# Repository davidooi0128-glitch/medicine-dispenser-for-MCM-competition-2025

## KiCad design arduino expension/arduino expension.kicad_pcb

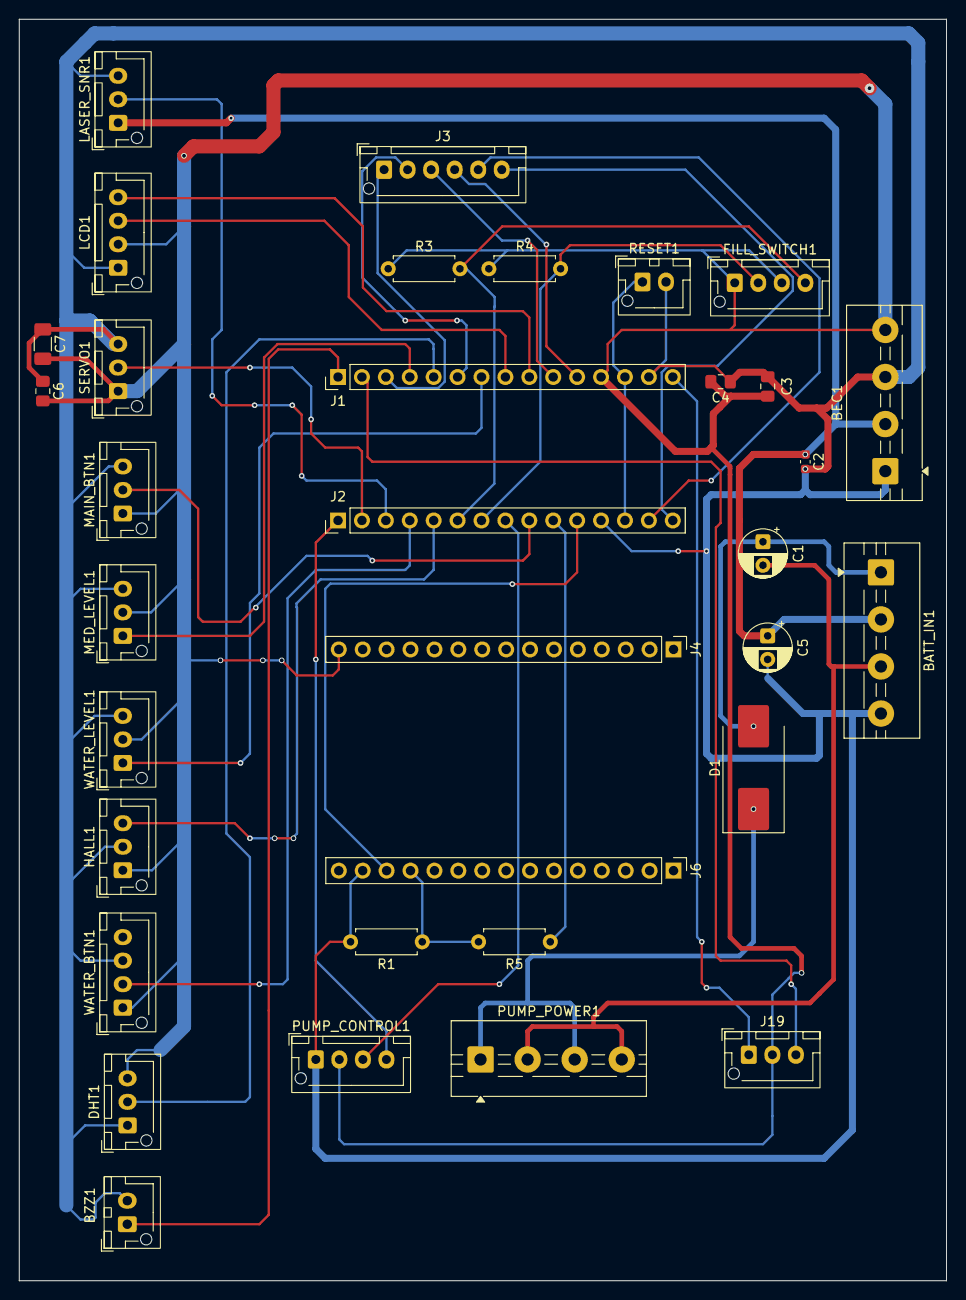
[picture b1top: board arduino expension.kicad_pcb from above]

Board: 2 copper layers, 98.5 x 134.0 mm, 34 parts (0 on the bottom side), 33 nets.

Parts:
BATT_IN1: Conn_01x04_Pin; TerminalBlock_MaiXu_MX126-5.0-04P_1x04_P5.00mm
BEC1: Conn_01x04_Pin; TerminalBlock_MaiXu_MX126-5.0-04P_1x04_P5.00mm
BZZ1: Conn_01x02_Pin; JST_XH_B2B-XH-AM_1x02_P2.50mm_Vertical
C1, C5: 47uF; CP_Radial_D5.0mm_P2.50mm
C2: 0.1Uf; C_0603_1608Metric
C3: 10uF; C_0805_2012Metric_Pad1.18x1.45mm_HandSolder
C4, C6: 100nF; C_0805_2012Metric_Pad1.18x1.45mm_HandSolder
C7: 10uF; C_1206_3216Metric_Pad1.33x1.80mm_HandSolder
D1: D; D_SMC_Handsoldering
DHT1: Conn_01x03_Pin; JST_XH_B3B-XH-AM_1x03_P2.50mm_Vertical
FILL_SWITCH1: Conn_01x04_Pin; JST_XH_B4B-XH-AM_1x04_P2.50mm_Vertical
HALL1: Conn_01x03_Pin; JST_XH_B3B-XH-AM_1x03_P2.50mm_Vertical
J1: Analog; PinHeader_1x15_P2.54mm_Vertical
J2: Digital; PinHeader_1x15_P2.54mm_Vertical
J3: Conn_01x06_Pin; JST_XH_B6B-XH-AM_1x06_P2.50mm_Vertical
J4, J6: Conn_01x15_Socket; PinHeader_1x15_P2.54mm_Vertical
J19: Conn_01x03_Pin; JST_XH_B3B-XH-AM_1x03_P2.50mm_Vertical
LASER_SNR1: Conn_01x03_Pin; JST_XH_B3B-XH-AM_1x03_P2.50mm_Vertical
LCD1: Conn_01x04_Pin; JST_XH_B4B-XH-AM_1x04_P2.50mm_Vertical
MAIN_BTN1: Conn_01x03_Pin; JST_XH_B3B-XH-AM_1x03_P2.50mm_Vertical
MED_LEVEL1: Conn_01x03_Pin; JST_XH_B3B-XH-AM_1x03_P2.50mm_Vertical
PUMP_CONTROL1: Conn_01x04_Pin; JST_XH_B4B-XH-AM_1x04_P2.50mm_Vertical
PUMP_POWER1: Conn_01x04_Pin; TerminalBlock_MaiXu_MX126-5.0-04P_1x04_P5.00mm
R1: 2K; R_Axial_DIN0207_L6.3mm_D2.5mm_P7.62mm_Horizontal
R3, R4: 10K; R_Axial_DIN0207_L6.3mm_D2.5mm_P7.62mm_Horizontal
R5: 1K; R_Axial_DIN0207_L6.3mm_D2.5mm_P7.62mm_Horizontal
RESET1: Conn_01x02_Pin; JST_XH_B2B-XH-AM_1x02_P2.50mm_Vertical
SERVO1: Conn_01x03_Pin; JST_XH_B3B-XH-AM_1x03_P2.50mm_Vertical
WATER_BTN1: Conn_01x03_Pin; JST_XH_B4B-XH-AM_1x04_P2.50mm_Vertical
WATER_LEVEL1: Conn_01x03_Pin; JST_XH_B3B-XH-AM_1x03_P2.50mm_Vertical

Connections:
+3V3: J1.2, J19.3
+5V: BEC1.4, C3.2, C4.2, C6.2, C7.2, DHT1.3, FILL_SWITCH1.1, FILL_SWITCH1.3, HALL1.1, J1.12, J4.15 (Pin_15_15), J19.2, LCD1.2, MAIN_BTN1.1, MED_LEVEL1.2, PUMP_CONTROL1.2, R3.1, R4.1, SERVO1.1, WATER_BTN1.1, WATER_LEVEL1.2
+15V: BATT_IN1.2, BEC1.2, C2.1, C5.1, LASER_SNR1.1
+24V: D1.1 (K), PUMP_POWER1.1, PUMP_POWER1.3
/A0: J1.4, MED_LEVEL1.1
/A1: DHT1.2, J1.5
/A2: J1.6, J3.2
/A3: J1.7, WATER_LEVEL1.1
/A4/SDA: J1.8, LCD1.3
/A5/SCL: J1.9, LCD1.4
/A6: J1.10, J3.3
/A7: J1.11, J3.4
/AREF: J1.3, J3.1
/D0/RX: J2.14, J3.5
/D1/TX: J2.15, J3.6
/D2: J2.11, J6.13
/D3: J2.10, R5.1
/D4: J2.9, MAIN_BTN1.2
/D5: J2.8, PUMP_CONTROL1.3
/D6: FILL_SWITCH1.2, J2.7, R4.2
/D7: FILL_SWITCH1.4, J2.6, R3.2
/D8: HALL1.3, J2.5
/D9: J2.4, WATER_BTN1.2
/D10: J2.3, LASER_SNR1.2
/D11: J2.2, SERVO1.2
/D12: J2.1, PUMP_CONTROL1.4
/D13: BZZ1.1, J1.1
/~RESET: J1.13, J2.13, RESET1.1
GND: BATT_IN1.4, BEC1.1, BEC1.3, BZZ1.2, C2.2, C3.1, C4.1, C5.2, C6.1, C7.1, DHT1.1, HALL1.2, J1.14, J2.12, J6.14, LASER_SNR1.3, LCD1.1, MAIN_BTN1.3, MED_LEVEL1.3, PUMP_CONTROL1.1, R1.2, RESET1.2, SERVO1.3, WATER_BTN1.3, WATER_LEVEL1.3
GND1: BATT_IN1.3, C1.2, PUMP_POWER1.2, PUMP_POWER1.4
unnamed: BATT_IN1.1, C1.1, D1.2 (A)
unnamed: J6.12, R1.1, R5.2
VCC: J1.15, J19.1

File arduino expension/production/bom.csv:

Designator,Footprint,Quantity,Value,LCSC Part #
"BATT_IN1, BEC1, PUMP_POWER1",TerminalBlock_MaiXu_MX126-5.0-04P_1x04_P5.00mm,3,Conn_01x04_Pin,
"BZZ1, RESET1",JST_XH_B2B-XH-AM_1x02_P2.50mm_Vertical,2,Conn_01x02_Pin,
"C1, C5",CP_Radial_D5.0mm_P2.50mm,2,47uF,
C2,0603,1,0.1Uf,
C3,0805,1,10uF,
"C4, C6",0805,2,100nF,
C7,1206,1,10uF,
D1,D_SMC_Handsoldering,1,D,
"DHT1, HALL1, J19, LASER_SNR1, MAIN_BTN1, MED_LEVEL1, SERVO1, WATER_LEVEL1",JST_XH_B3B-XH-AM_1x03_P2.50mm_Vertical,8,Conn_01x03_Pin,
"FILL_SWITCH1, LCD1, PUMP_CONTROL1",JST_XH_B4B-XH-AM_1x04_P2.50mm_Vertical,3,Conn_01x04_Pin,
J1,PinHeader_1x15_P2.54mm_Vertical,1,Analog,
J2,PinHeader_1x15_P2.54mm_Vertical,1,Digital,
J3,JST_XH_B6B-XH-AM_1x06_P2.50mm_Vertical,1,Conn_01x06_Pin,
"J4, J6",PinHeader_1x15_P2.54mm_Vertical,2,Conn_01x15_Socket,
R1,R_Axial_DIN0207_L6.3mm_D2.5mm_P7.62mm_Horizontal,1,2K,
"R3, R4",R_Axial_DIN0207_L6.3mm_D2.5mm_P7.62mm_Horizontal,2,10K,
R5,R_Axial_DIN0207_L6.3mm_D2.5mm_P7.62mm_Horizontal,1,1K,
WATER_BTN1,JST_XH_B4B-XH-AM_1x04_P2.50mm_Vertical,1,Conn_01x03_Pin,
